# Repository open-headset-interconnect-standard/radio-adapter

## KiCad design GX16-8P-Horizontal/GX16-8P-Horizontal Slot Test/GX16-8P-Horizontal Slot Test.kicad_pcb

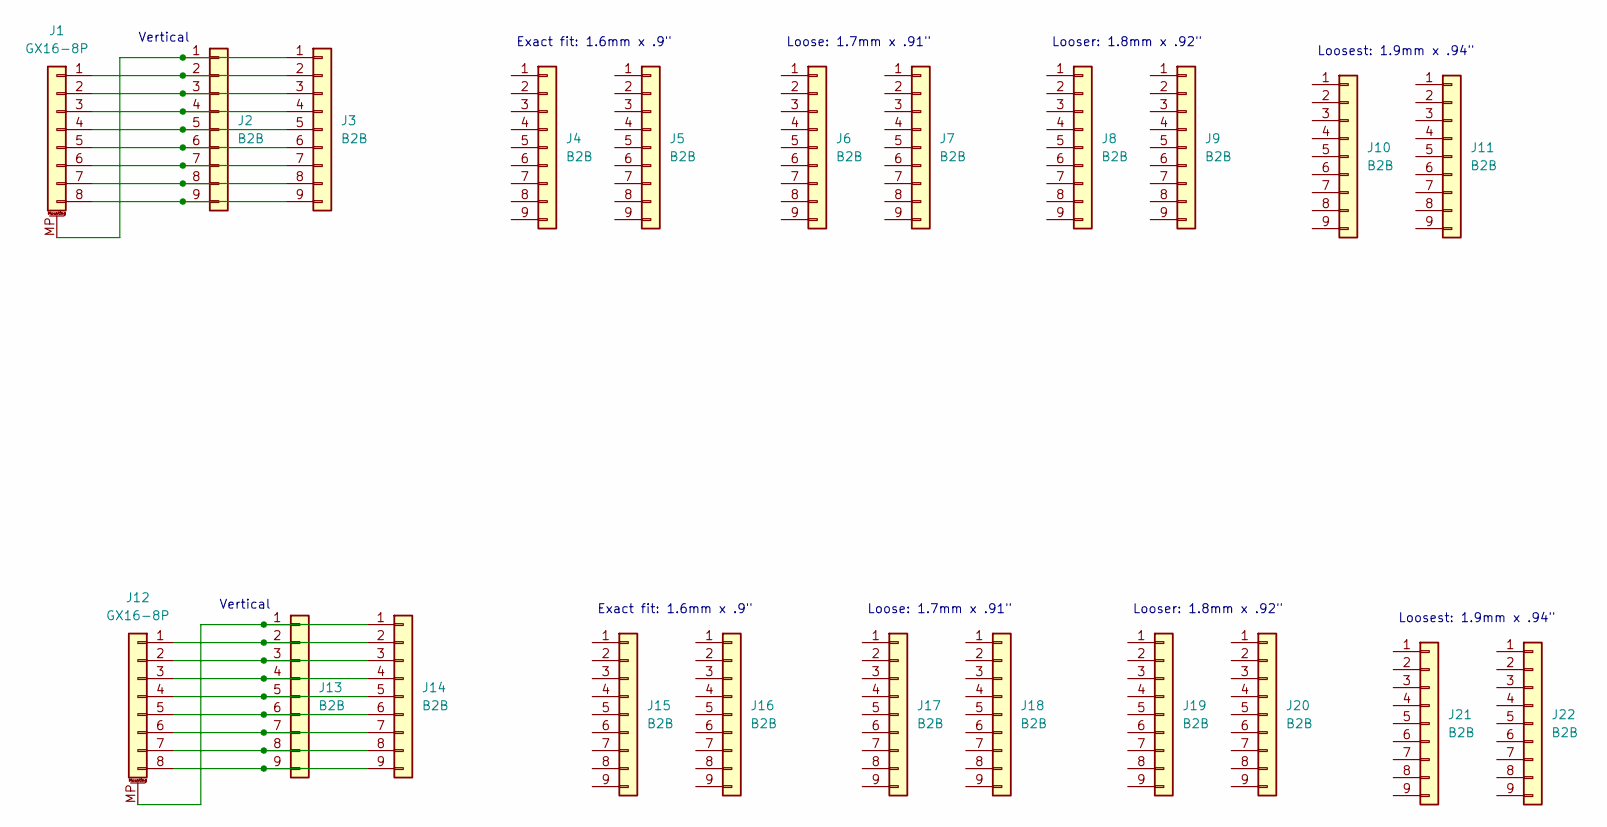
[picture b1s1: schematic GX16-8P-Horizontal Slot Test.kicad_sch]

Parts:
J1, J12: GX16-8P; Conn_GX16-8_8pin_Aviation
J2, J4, J6, J8, J10, J13, J15, J17, J19, J21: B2B; Conn_B2B-RA_2.54mm_9pin_LtoR
J3, J5, J7, J9, J11, J14, J16, J18, J20, J22: B2B; Conn_B2B-RA_2.54mm_9pin_RtoL

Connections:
unnamed: J1.1, J2.2, J3.2
unnamed: J1.2, J2.3, J3.3
unnamed: J1.3, J2.4, J3.4
unnamed: J1.4, J2.5, J3.5
unnamed: J1.5, J2.6, J3.6
unnamed: J1.6, J2.7, J3.7
unnamed: J1.7, J2.8, J3.8
unnamed: J1.8, J2.9, J3.9
unnamed: J1.MP (MountPin), J2.1, J3.1
unnamed: J12.1, J13.2, J14.2
unnamed: J12.2, J13.3, J14.3
unnamed: J12.3, J13.4, J14.4
unnamed: J12.4, J13.5, J14.5
unnamed: J12.5, J13.6, J14.6
unnamed: J12.6, J13.7, J14.7
unnamed: J12.7, J13.8, J14.8
unnamed: J12.8, J13.9, J14.9
unnamed: J12.MP (MountPin), J13.1, J14.1

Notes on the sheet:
Exact fit: 1.6mm x .9"
Loosest: 1.9mm x .94"
Looser: 1.8mm x .92"
Loose: 1.7mm x .91"
Vertical

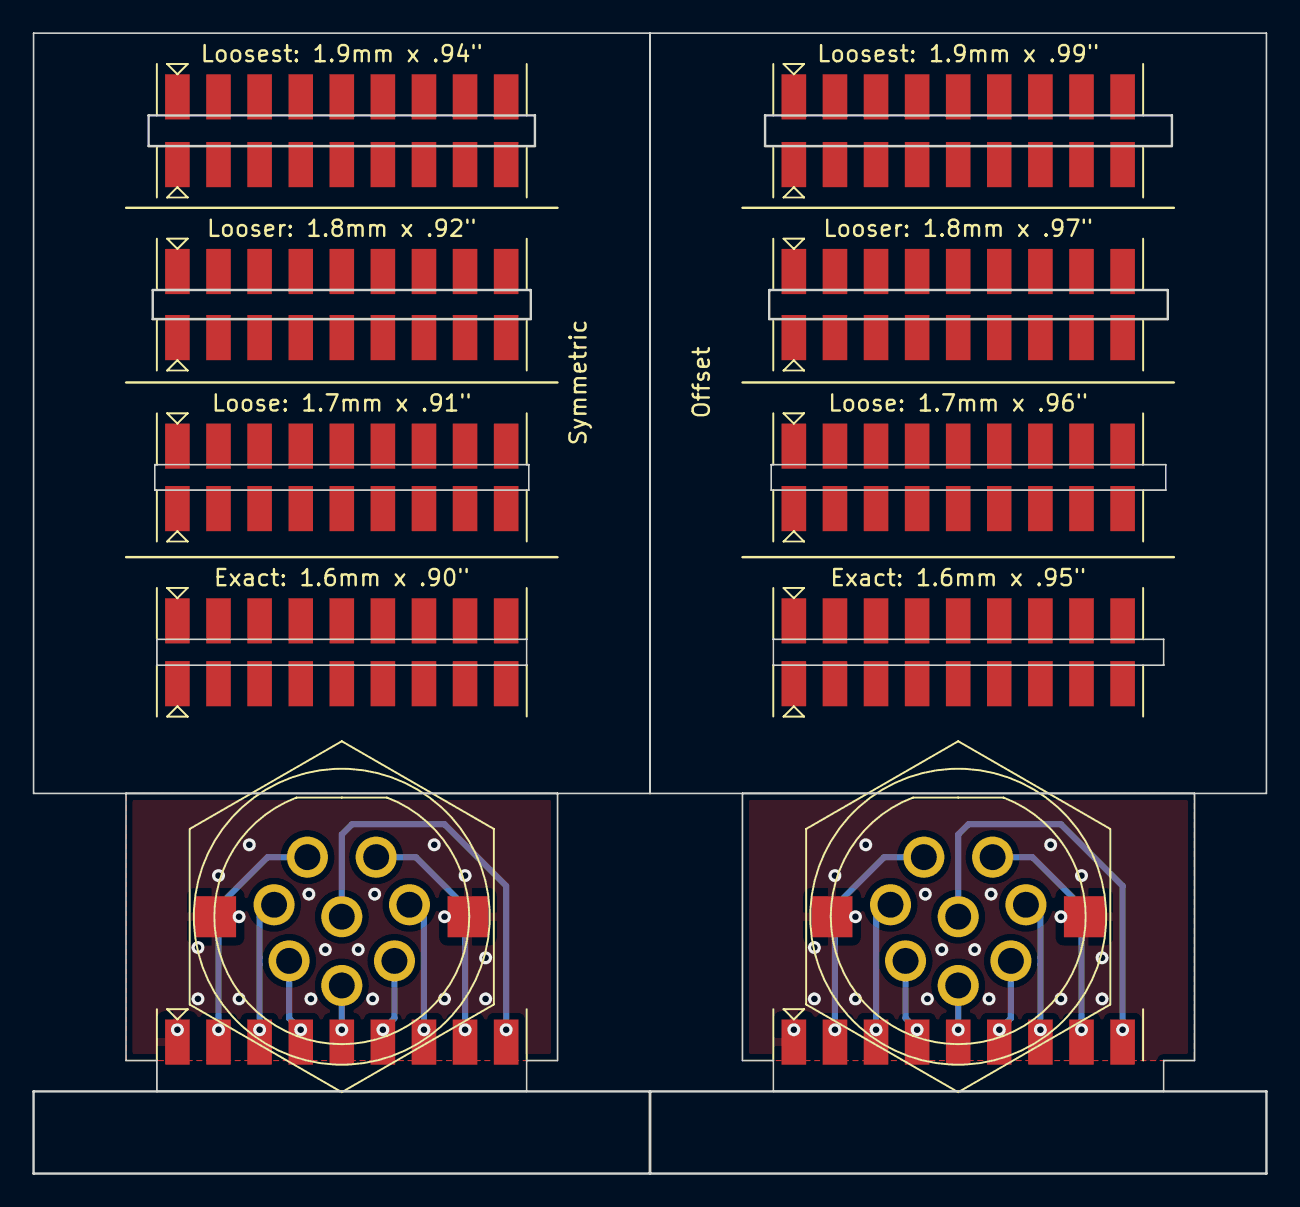
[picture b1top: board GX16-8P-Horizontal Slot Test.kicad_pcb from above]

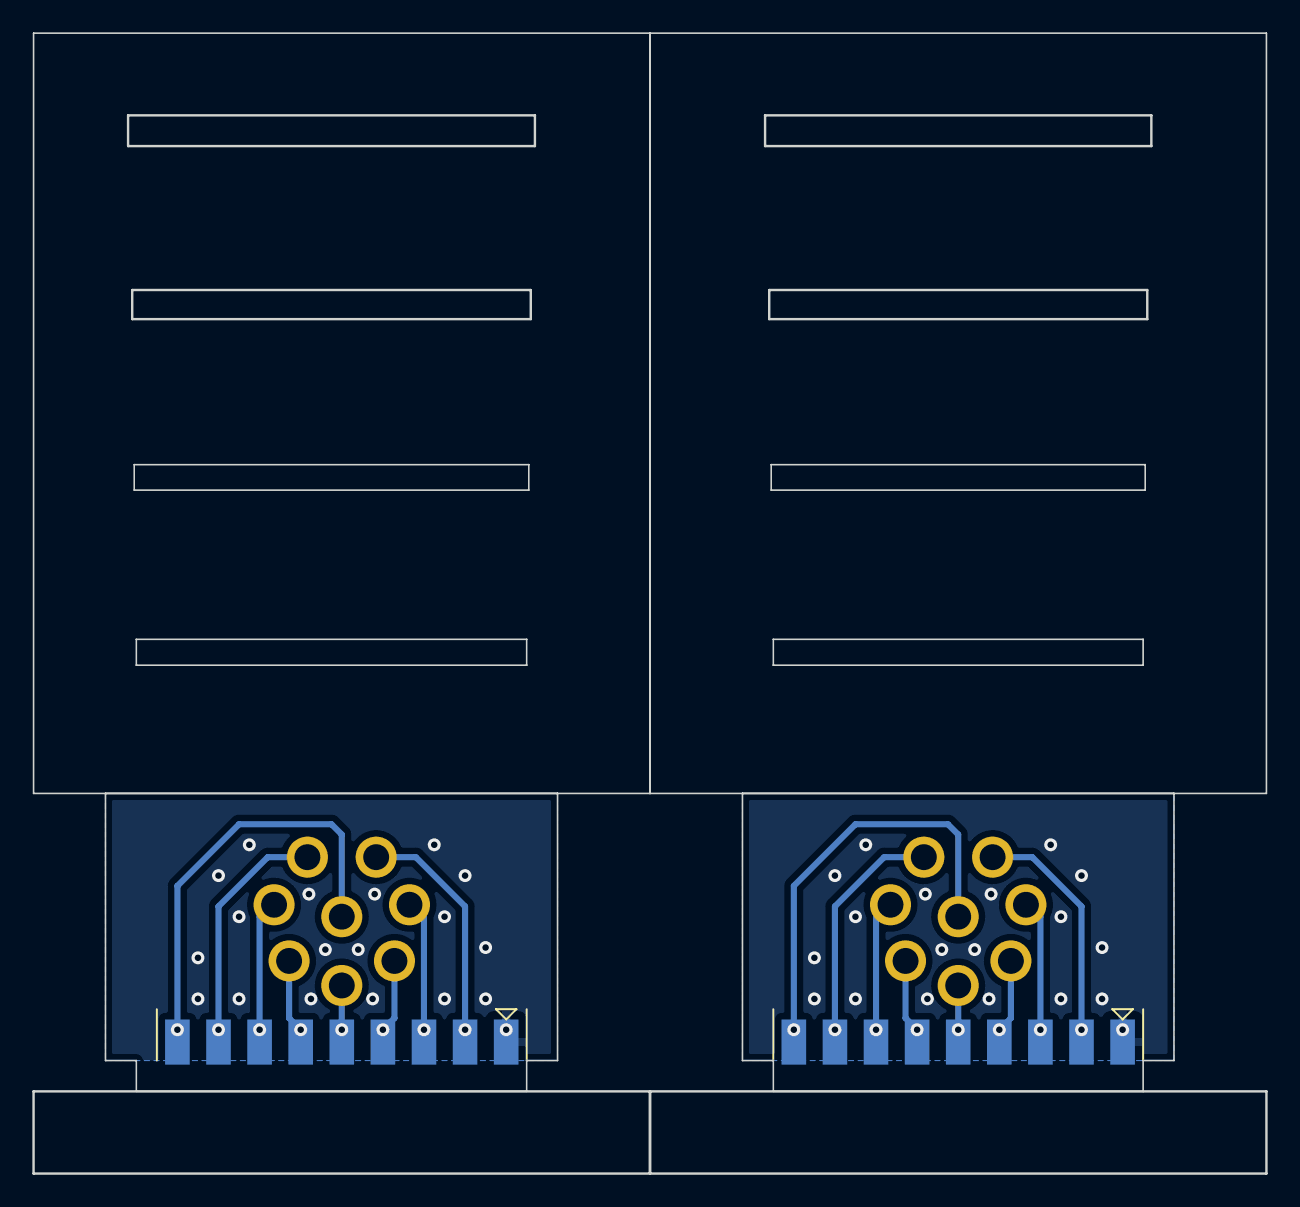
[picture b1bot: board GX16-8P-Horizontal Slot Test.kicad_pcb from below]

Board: 2 copper layers, 76.2 x 70.5 mm, 22 parts (2 on the bottom side), 18 nets.

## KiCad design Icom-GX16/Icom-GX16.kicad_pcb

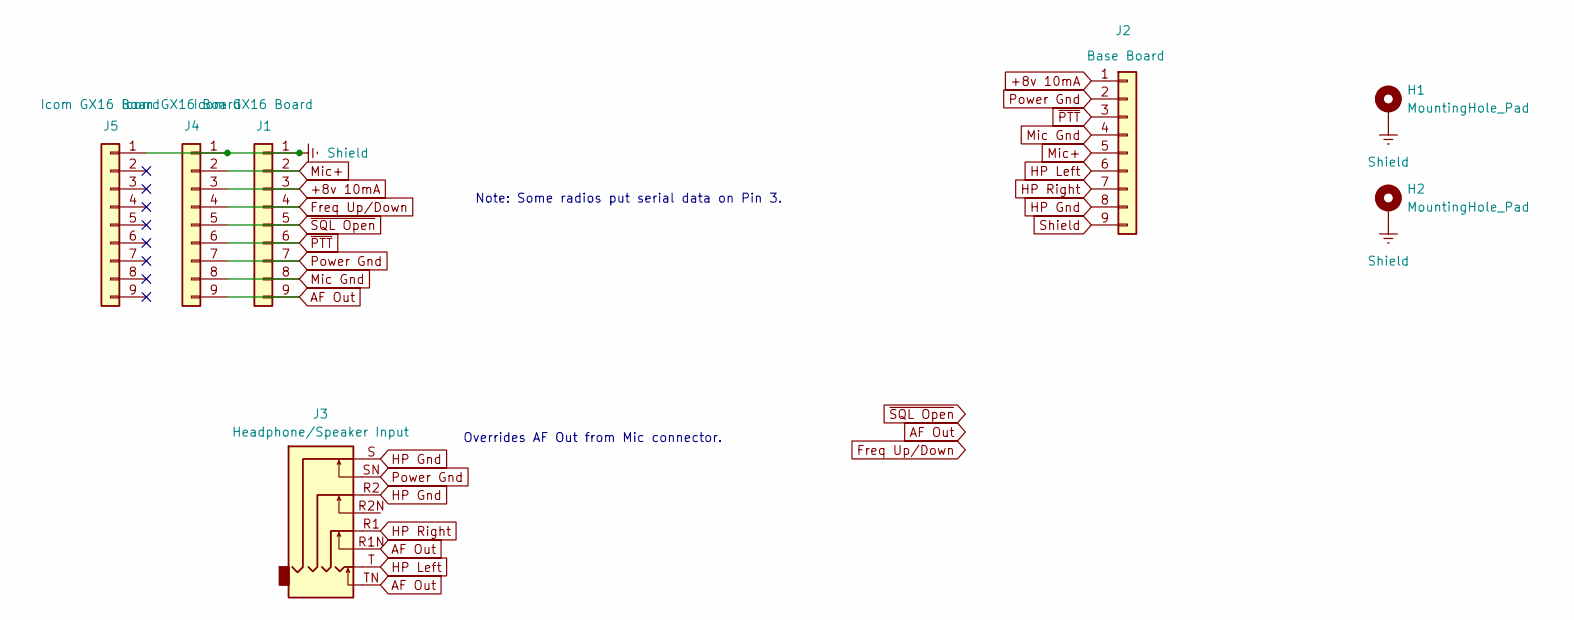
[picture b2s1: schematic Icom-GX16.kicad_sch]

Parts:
H1, H2: MountingHole_Pad; MountingHole_3.2mm_M3_Pad
J1: Icom GX16 Board; Conn_B2B-RA_2.54mm_9pin_RtoL
J2: Base Board; Conn_B2B-RA_2.54mm_Castelated_9pin_RtoL
J3: Headphone/Speaker Input; Conn_3.5mm-PJ-393_SMT-C668609_TH-C145811
J4, J5: Icom GX16 Board; Conn_B2B-RA_2.54mm_9pin_LtoR

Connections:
+8v 10mA: J1.3, J2.1, J4.3
AF Out: J1.9, J3.R1N, J3.TN, J4.9
Freq Up/Down: J1.4, J4.4
HP Gnd: J2.8, J3.R2, J3.S
HP Left: J2.6, J3.T
HP Right: J2.7, J3.R1
Mic Gnd: J1.8, J2.4, J4.8
Mic+: J1.2, J2.5, J4.2
Power Gnd: J1.7, J2.2, J3.SN, J4.7
Shield: H1.1, H2.1, J1.1, J2.9, J4.1, J5.1
~PTT: J1.6, J2.3, J4.6
~SQL Open: J1.5, J4.5

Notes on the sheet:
Note: Some radios put serial data on Pin 3.
Overrides AF Out from Mic connector.

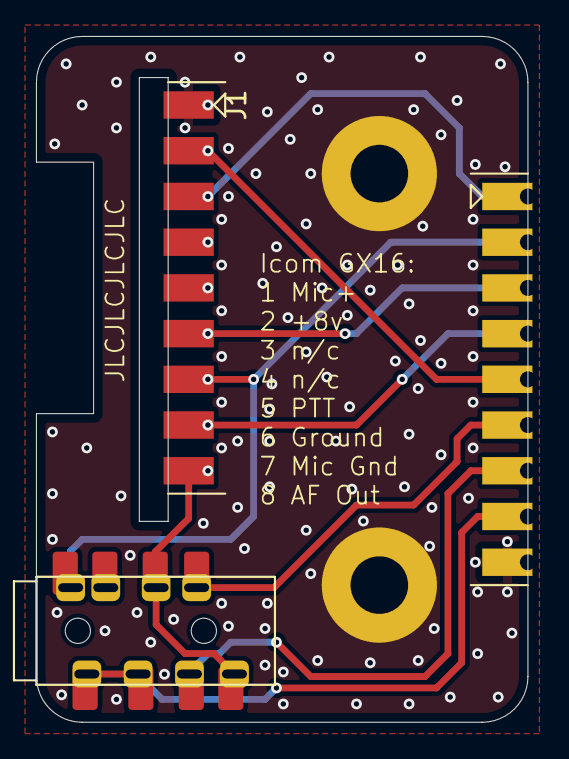
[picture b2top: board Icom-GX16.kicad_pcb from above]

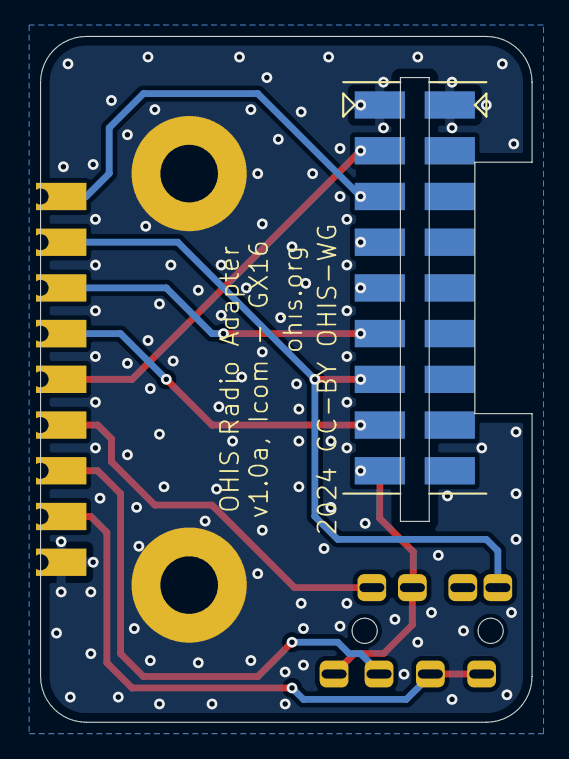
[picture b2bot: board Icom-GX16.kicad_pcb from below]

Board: 2 copper layers, 27.3 x 38.1 mm, 7 parts (2 on the bottom side), 12 nets.

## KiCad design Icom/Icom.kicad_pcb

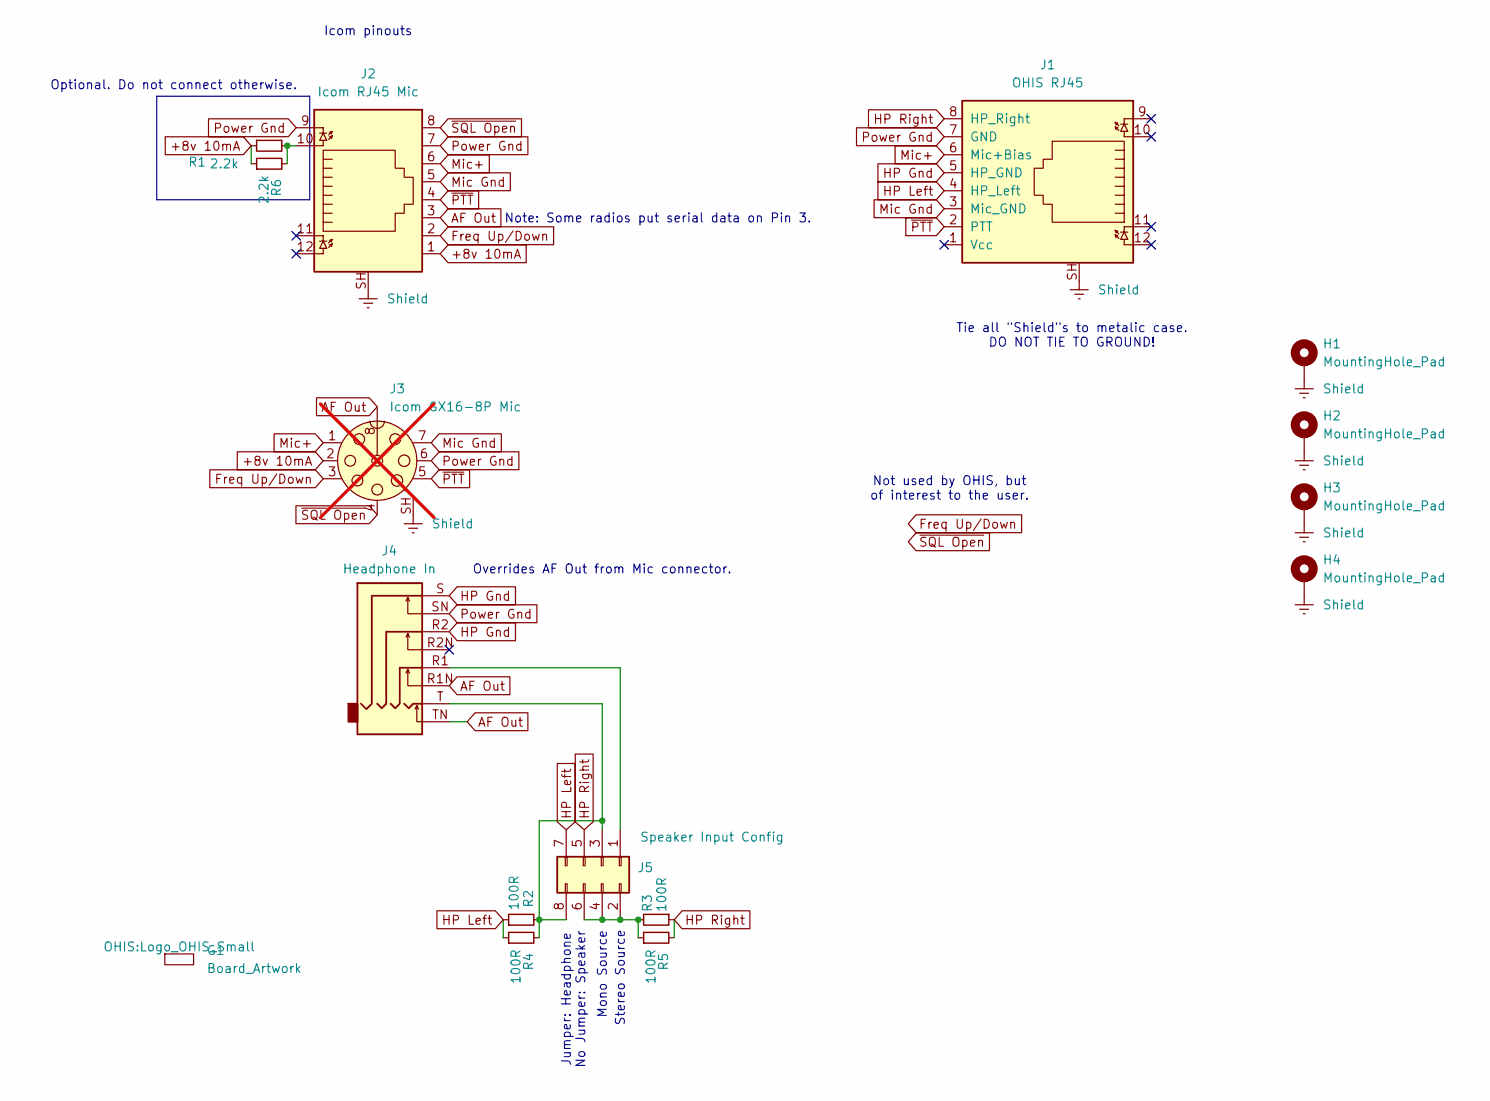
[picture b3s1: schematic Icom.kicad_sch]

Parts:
G1: Board_Artwork; Logo_OHIS_Small
H1, H2, H3, H4: MountingHole_Pad; MountingHole_3.2mm_M3_Pad
J1: OHIS RJ45; RJ45_Amphenol_RJHSE538X; LCSC C138392
J2: Icom RJ45 Mic; RJ45_Amphenol_RJHSE538X; LCSC C138392
J3: Icom GX16-8P Mic; not fitted
J4: Headphone In; Conn_3.5mm-PJ-393_SMT-C668609_TH-C145811; LCSC C6688609
J5: Speaker Input Config; PinHeader_2x04_P2.54mm_Horizontal; LCSC C9139
R1: 2.2k; R_1206_3216Metric
R2, R3: 100R; R_1206_3216Metric
R4, R5: 100R; R_Axial_DIN0207_L6.3mm_D2.5mm_P7.62mm_Horizontal
R6: 2.2k; R_Axial_DIN0207_L6.3mm_D2.5mm_P7.62mm_Horizontal

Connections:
+8v 10mA: J2.1, J3.2, R1.1, R6.1
AF Out: J2.3, J3.8, J4.R1N, J4.TN
Freq Up/Down: J2.2, J3.3
HP Gnd: J1.5 (HP_GND), J4.R2, J4.S
HP Left: J1.4 (HP_Left), J5.7, R2.1, R4.1
HP Right: J1.8 (HP_Right), J5.5, R3.1, R5.2
Mic Gnd: J1.3 (Mic_GND), J2.5, J3.7
Mic+: J1.6 (Mic+Bias), J2.6, J3.1
unnamed: J2.10, R1.2, R6.2
unnamed: J4.R1, J5.1
unnamed: J5.2, J5.4, J5.6, R3.2, R5.1
unnamed: J4.T, J5.3, J5.8, R2.2, R4.2
Power Gnd: J1.7 (GND), J2.7, J2.9, J3.6, J4.SN
Shield: H1.1, H2.1, H3.1, H4.1, J1.SH, J2.SH, J3.SH
~PTT: J1.2 (PTT), J2.4, J3.5
~SQL Open: J2.8, J3.4

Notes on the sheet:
Icom pinouts
Not used by OHIS, but of interest to the user.
Stereo Source
Overrides AF Out from Mic connector.
Jumper: Headphone No Jumper: Speaker
Note: Some radios put serial data on Pin 3.
Tie all "Shield"s to metalic case. DO NOT TIE TO GROUND!
Optional. Do not connect otherwise.
Mono Source

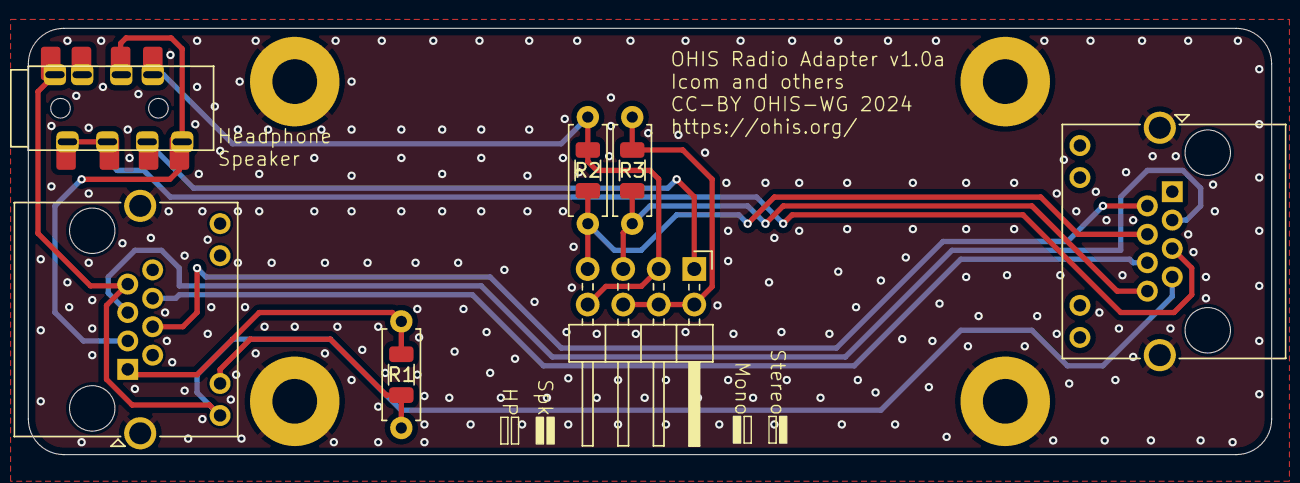
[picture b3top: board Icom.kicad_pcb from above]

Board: 2 copper layers, 88.9 x 30.5 mm, 15 parts (1 on the bottom side), 14 nets.

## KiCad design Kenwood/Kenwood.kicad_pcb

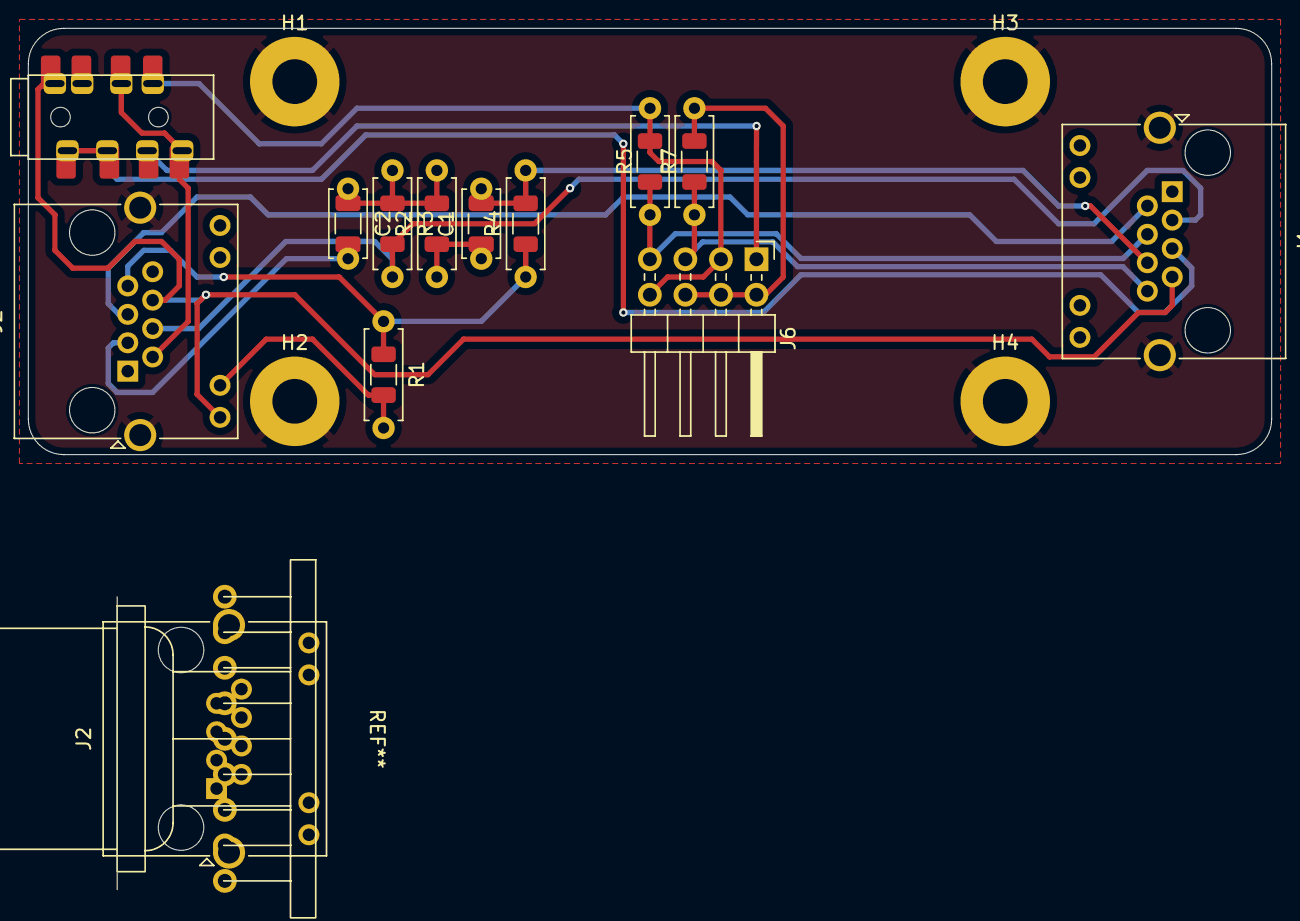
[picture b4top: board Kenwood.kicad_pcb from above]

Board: 2 copper layers, 88.9 x 30.5 mm, 26 parts (0 on the bottom side), 17 nets.

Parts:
C1, C2: 10uF; C_Disc_D4.7mm_W2.5mm_P5.00mm
C3, C4: 10uF; C_1206_3216Metric
G1: Board_Artwork; Logo_OHIS_Small
H1, H2, H3, H4: MountingHole_Pad; MountingHole_3.2mm_M3_Pad
J1: OHIS RJ45; RJ45_Amphenol_RJHSE538X
J2, J2#2: Kenwood RJ45 Mic; RJ45_Amphenol_RJHSE538X
J4: Headphone In; Conn_3.5mm-PJ-393_SMT-C668609_TH-C145811
J6: Speaker Input Config; PinHeader_2x04_P2.54mm_Horizontal
R1, R2: 1k; R_Axial_DIN0207_L6.3mm_D2.5mm_P7.62mm_Horizontal
R3, R6, R8: 100R; R_Axial_DIN0207_L6.3mm_D2.5mm_P7.62mm_Horizontal
R4: 6.2k; R_Axial_DIN0207_L6.3mm_D2.5mm_P7.62mm_Horizontal
R5, R7, R9: 100R; R_1206_3216Metric
R10, R12: 1k; R_1206_3216Metric
R11: 6.2k; R_1206_3216Metric

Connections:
+8v 10mA: J2#2.7, R1.1, R4.1, R11.1, R12.1
AF Out: J2#2.2, J4.R1N, J4.TN
HP Gnd: J1.5 (HP_GND), J4.R2, J4.S
HP Left: J1.4 (HP_Left), J6.7, R5.1, R6.1
HP Right: J1.8 (HP_Right), J6.5, R7.1, R8.2
Mic Gnd: J1.3 (Mic_GND), J2#2.4, R3.2, R9.2
Mic+: C2.2, C4.2, J2#2.3
unnamed: C1.1, C3.1, R2.1, R10.1
unnamed: C2.1, C4.1, R2.2, R3.1, R9.1, R10.2
unnamed: J2#2.10, R1.2, R12.2
unnamed: J4.R1, J6.1
unnamed: J6.2, J6.4, J6.6, R7.2, R8.1
unnamed: J4.T, J6.3, J6.8, R5.2, R6.2
OHIS Mic+: C1.2, C3.2, J1.6 (Mic+Bias), R4.2, R11.2
Power Gnd: J1.7 (GND), J2#2.6, J2#2.9, J4.SN
Shield: H1.1, H2.1, H3.1, H4.1, J1.SH, J2#2.SH
~PTT: J1.2 (PTT), J2#2.5

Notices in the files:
Icom-GX16/Icom-GX16.kicad_pcb:
2024 CC-BY OHIS-WG
Icom/Icom.kicad_pcb:
CC-BY OHIS-WG 2024
